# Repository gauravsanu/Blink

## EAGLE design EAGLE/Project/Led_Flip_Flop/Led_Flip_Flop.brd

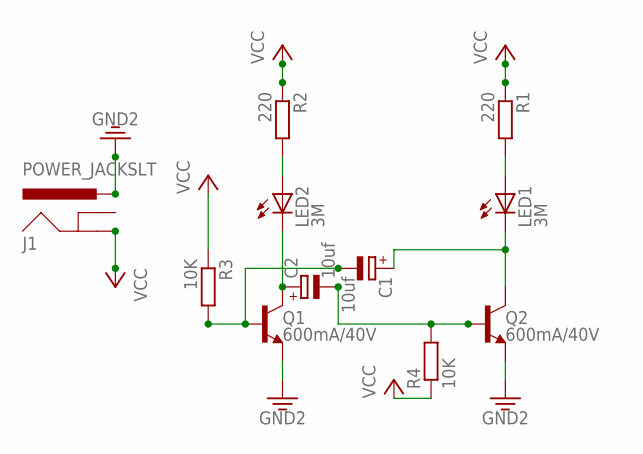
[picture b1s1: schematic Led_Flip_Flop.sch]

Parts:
C1, C2: 10uf; E1,8-4
J1: POWER_JACKSLT; POWER_JACK_SLOT
LED1, LED2: 3M; LED5MM
Q1, Q2: 600mA/40V; TO-92
R1, R2: 220; 0207/10
R3, R4: 10K; 0207/10

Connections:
3.3V: J1.PWR, Q1.3 (E), Q2.3 (E)
unnamed: LED2.A, R2.2
unnamed: LED1.A, R1.2
unnamed: C2.+, LED2.K (C), Q1.1 (C)
unnamed: C1.-, Q1.2 (B), R3.2
unnamed: C2.-, Q2.2 (B), R4.2
unnamed: C1.+, LED1.K (C), Q2.1 (C)
VCC: J1.GND@2 (GND), R1.1, R2.1, R3.1, R4.1

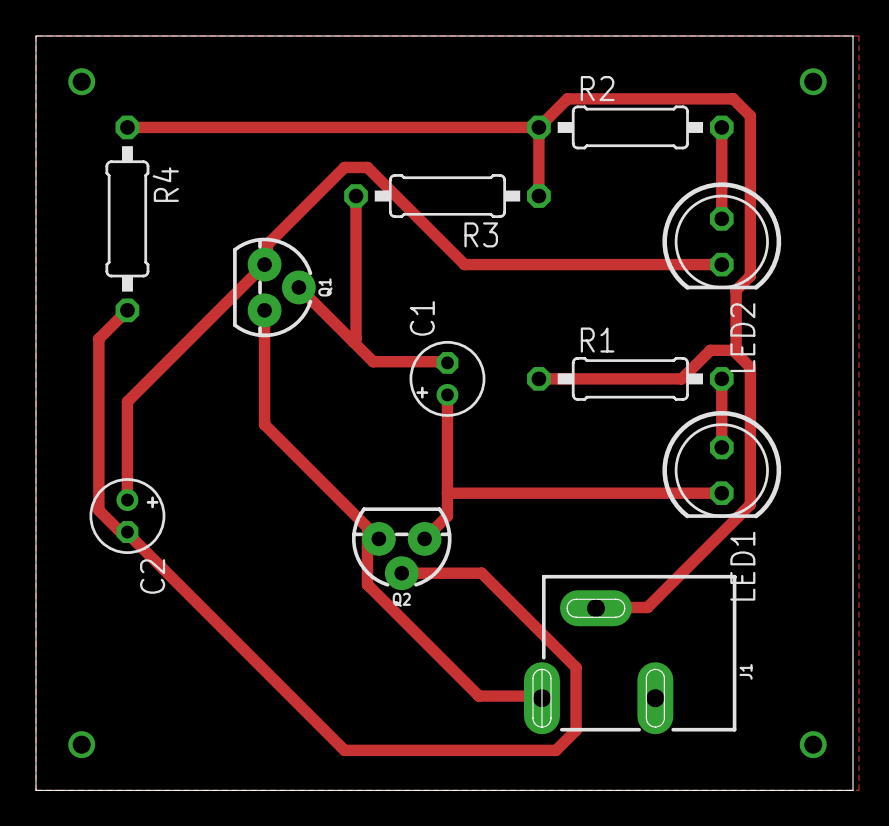
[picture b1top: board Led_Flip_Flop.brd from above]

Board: 2 copper layers, 45.4 x 41.9 mm, 11 parts (0 on the bottom side), 8 nets.

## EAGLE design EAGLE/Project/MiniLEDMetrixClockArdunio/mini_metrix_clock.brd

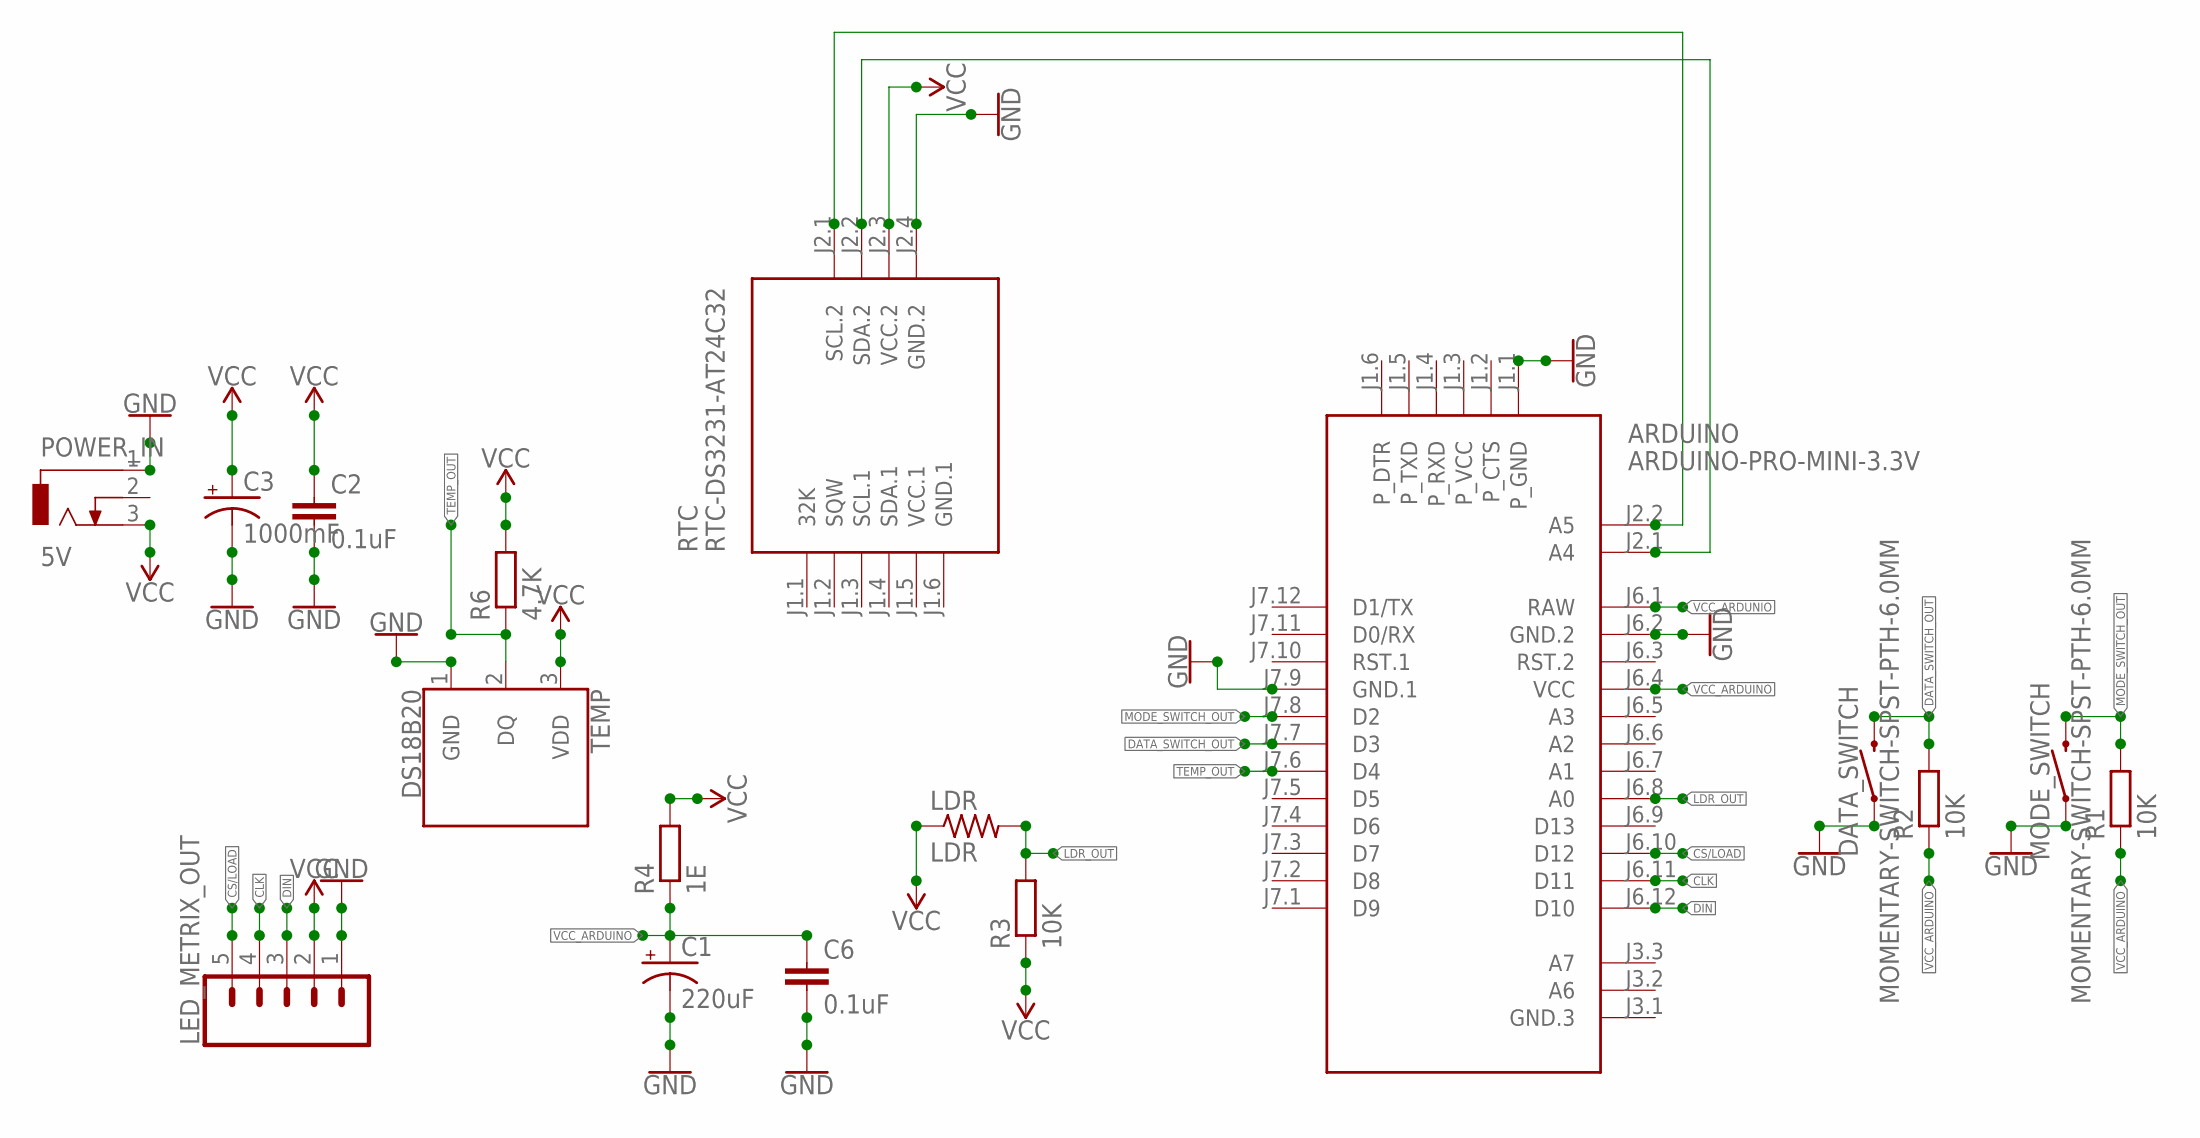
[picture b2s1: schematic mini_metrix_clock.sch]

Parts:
ARDUINO: ARDUINO-PRO-MINI-3.3V; ARDUINO-PRO-MINI
C1: 220uF; CPOL-RADIAL-2.5MM-6.5MM
C2, C6: 0.1uF; CAP-PTH-SMALL-KIT
C3: 1000mF; CPOL-RADIAL-5MM-10MM
DATA_SWITCH: MOMENTARY-SWITCH-SPST-PTH-6.0MM; TACTILE_SWITCH_PTH_6.0MM
LDR: LDR; 0204V
LED_METRIX_OUT: CONN_05PTH_LONGPADS; 1X05_LONGPADS
MODE_SWITCH: MOMENTARY-SWITCH-SPST-PTH-6.0MM; TACTILE_SWITCH_PTH_6.0MM
POWER_IN: 5V; DCJ0303
R1, R2, R3: 10K; 0207/7
R4: 1E; 0207/7
R6: 4.7K; 0207/7
RTC: RTC-DS3231-AT24C32
TEMP: DS18B20; TO-92-AMMO

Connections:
CLK: ARDUINO.J6.11 (D11), LED_METRIX_OUT.4
CS/LOAD: ARDUINO.J6.10 (D12), LED_METRIX_OUT.5
DATA_SWITCH_OUT: ARDUINO.J7.7 (D3), DATA_SWITCH.3 (2), R2.2
DIN: ARDUINO.J6.12 (D10), LED_METRIX_OUT.3
GND: ARDUINO.J1.1 (P_GND), ARDUINO.J6.2 (GND.2), ARDUINO.J7.9 (GND.1), C1.2 (-), C2.2, C3.-, C6.2, DATA_SWITCH.1, LED_METRIX_OUT.1, MODE_SWITCH.1, POWER_IN.1, RTC.J2.4 (GND.2), TEMP.1 (GND)
GND.1: RTC.J1.6 (GND.1)
LDR_OUT: ARDUINO.J6.8 (A0), LDR.2, R3.2
MODE_SWITCH_OUT: ARDUINO.J7.8 (D2), MODE_SWITCH.3 (2), R1.2
unnamed: ARDUINO.J2.1 (A4), RTC.J2.2 (SDA.2)
unnamed: ARDUINO.J2.2 (A5), RTC.J2.1 (SCL.2)
TEMP_OUT: ARDUINO.J7.6 (D4), R6.1, TEMP.2 (DQ)
VCC: C2.1, C3.+, LDR.1, LED_METRIX_OUT.2, POWER_IN.3, R3.1, R4.2, R6.2, RTC.J2.3 (VCC.2), TEMP.3 (VDD)
VCC.1: RTC.J1.5 (VCC.1)
VCC_ARDUINO: ARDUINO.J6.4 (VCC), C1.1 (+), C6.1, R1.1, R2.1, R4.1
VCC_ARDUNIO: ARDUINO.J6.1 (RAW)

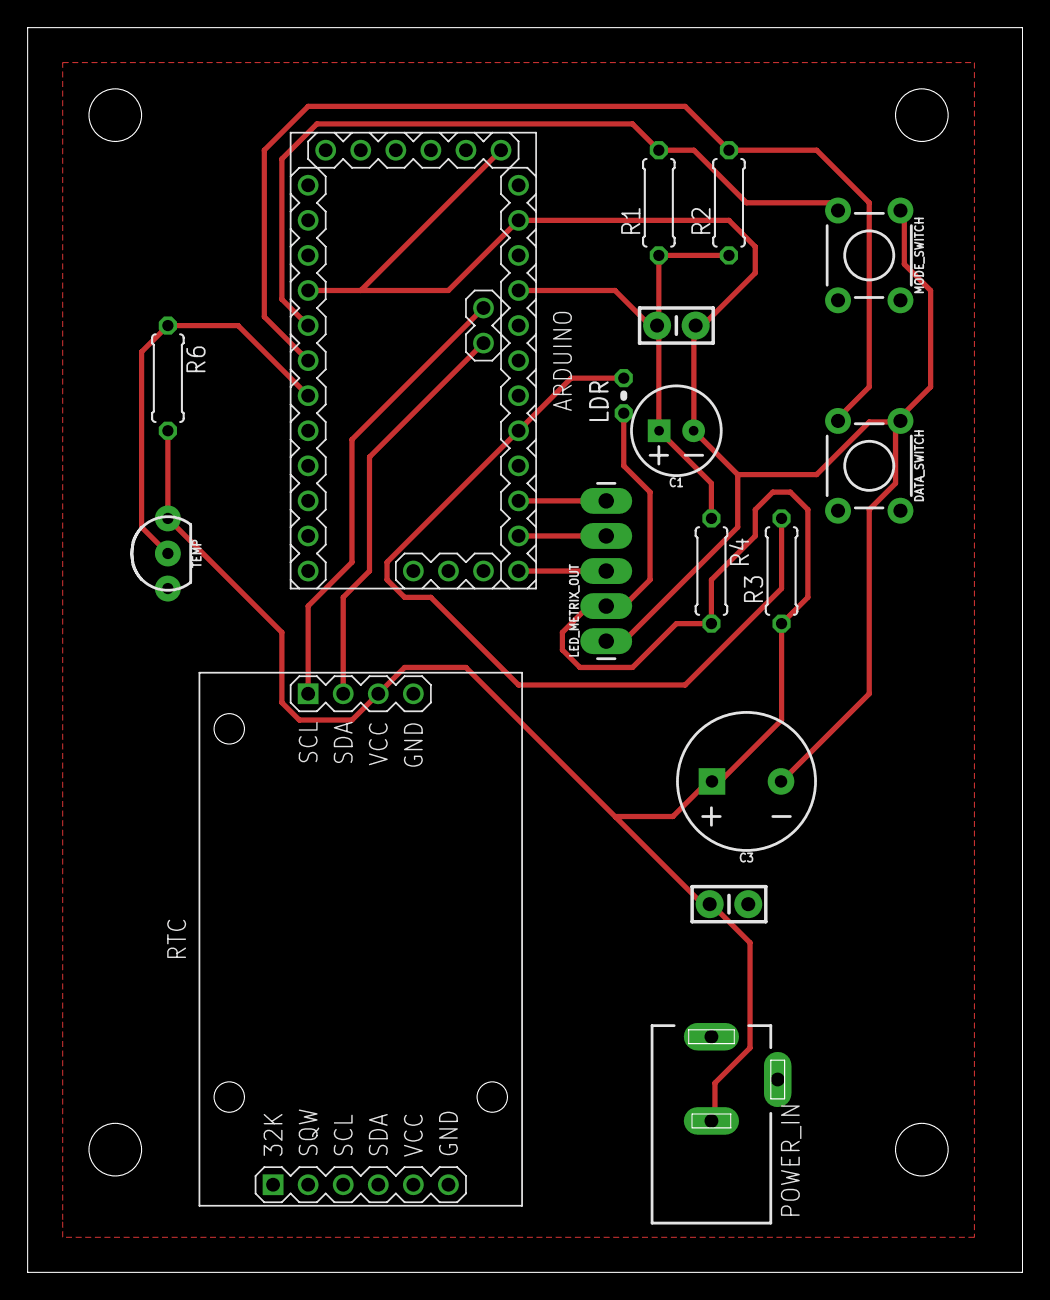
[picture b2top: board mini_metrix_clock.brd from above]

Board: 2 copper layers, 72.1 x 90.2 mm, 17 parts (0 on the bottom side), 12 nets.

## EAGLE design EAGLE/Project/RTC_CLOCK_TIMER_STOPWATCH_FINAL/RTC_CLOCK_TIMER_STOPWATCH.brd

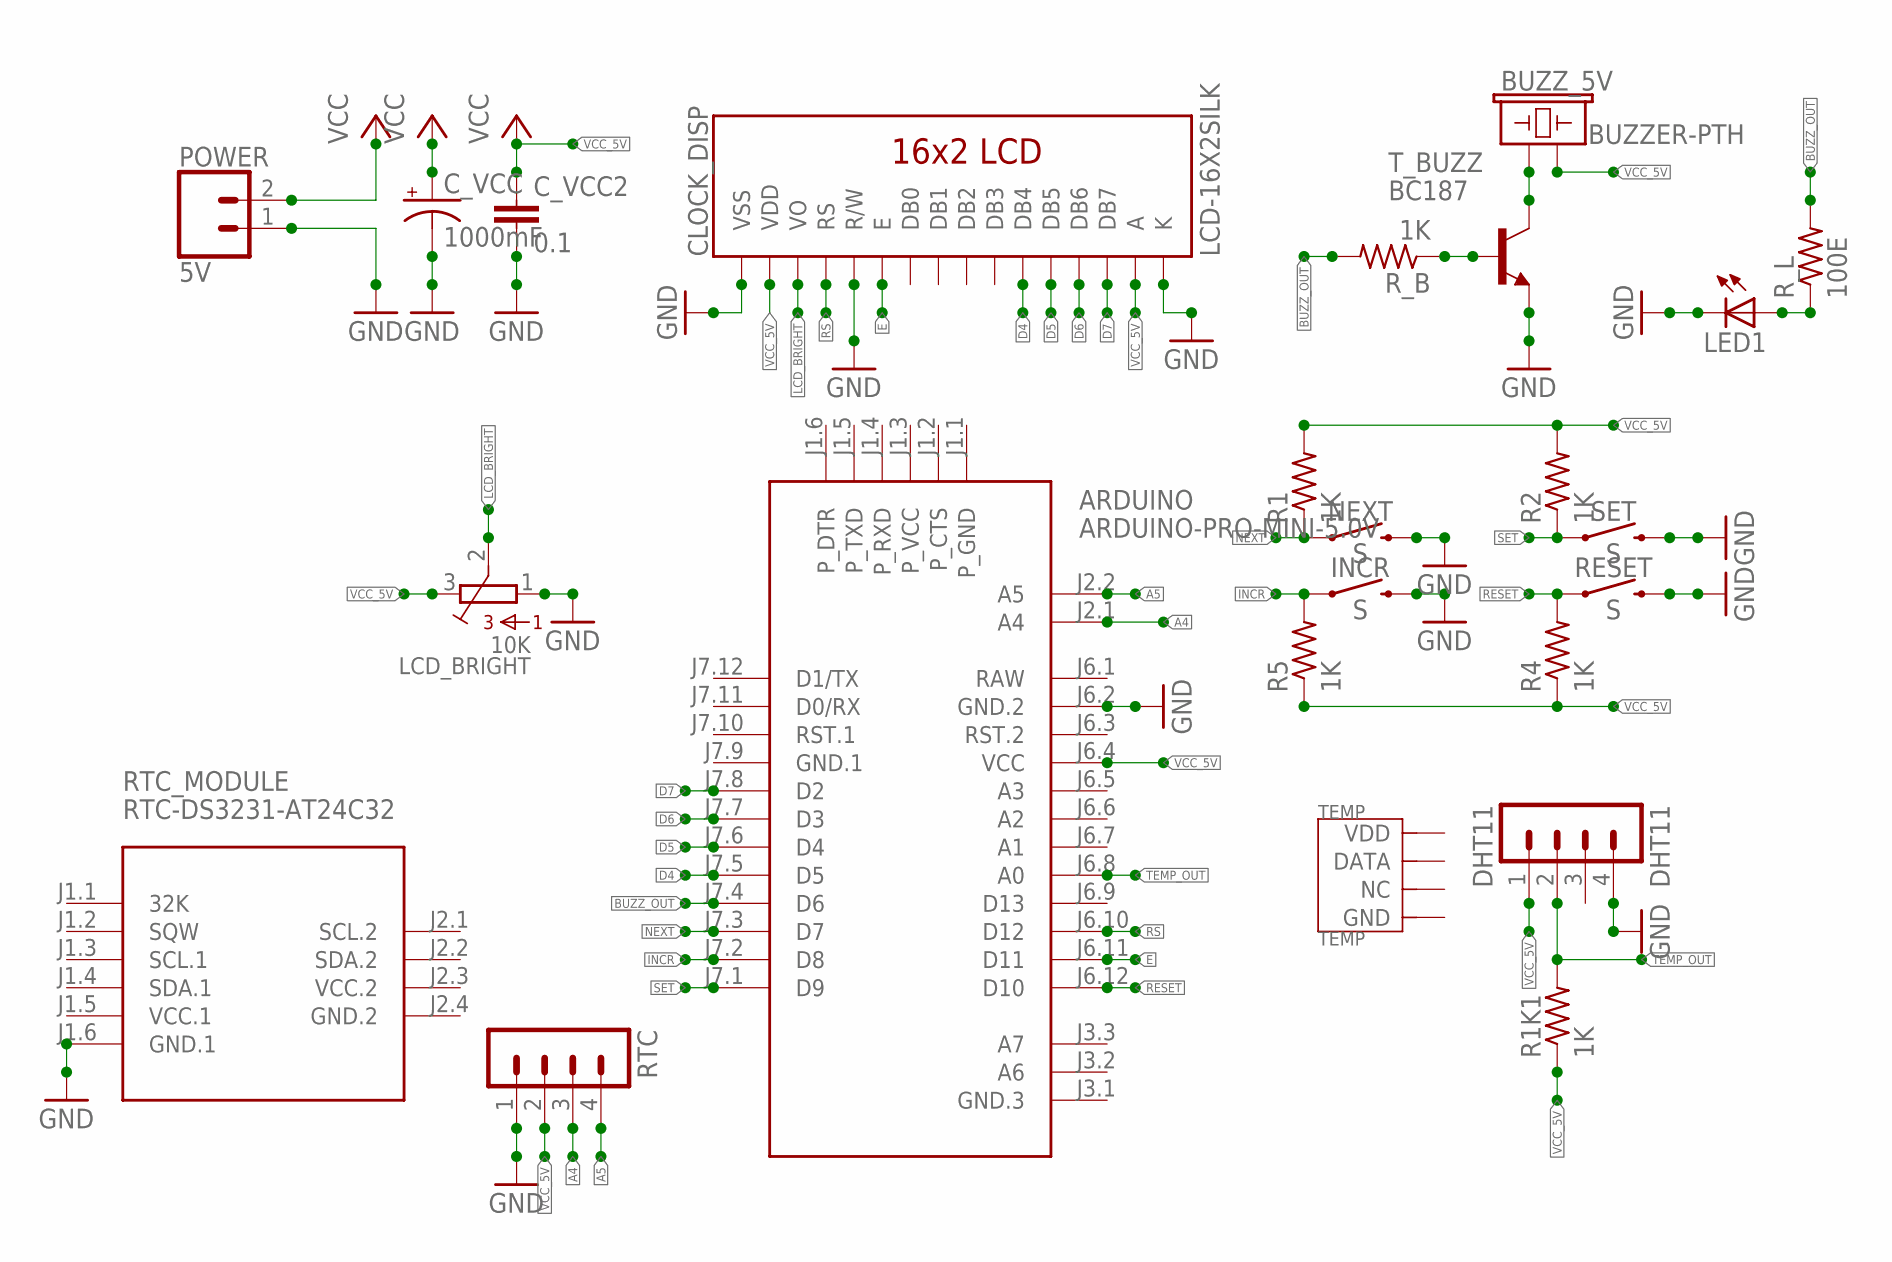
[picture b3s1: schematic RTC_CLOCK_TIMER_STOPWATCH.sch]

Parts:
ARDUINO: ARDUINO-PRO-MINI-5.0V; ARDUINO-PRO-MINI
BUZZ_5V: BUZZER-PTH; BUZZER-12MM
CLOCK_DISP: LCD-16X2SILK; LCD-16X2
C_VCC: 1000mF; CPOL-RADIAL-5MM-10MM
C_VCC2: 0.1; C050-024X044
DHT11: DHT11; MA04-1
INCR: S; TACTILE_SWITCH_PTH_6.0MM
LCD_BRIGHT: 10K; 3362P
LED1: LED5MM
NEXT: S; TACTILE_SWITCH_PTH_6.0MM
POWER: 5V; JST-2-PTH-KIT
R1, R1K1, R2, R4, R5: 1K; 0204/7
RESET: S; TACTILE_SWITCH_PTH_6.0MM
RTC: MA04-1
RTC_MODULE: RTC-DS3231-AT24C32
R_B: 1K; 0204/7
R_L: 100E; 0204/7
SET: S; TACTILE_SWITCH_PTH_6.0MM
TEMP: TEMP; SNR4-2.54-15.5X12.0X5.5MM
T_BUZZ: BC187; TO92-EBC-OVAL

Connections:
A4: ARDUINO.J2.1 (A4), RTC.3
A5: ARDUINO.J2.2 (A5), RTC.4
BUZZ_OUT: ARDUINO.J7.4 (D6), R_B.2, R_L.2
D4: ARDUINO.J7.5 (D5), CLOCK_DISP.11 (DB4)
D5: ARDUINO.J7.6 (D4), CLOCK_DISP.12 (DB5)
D6: ARDUINO.J7.7 (D3), CLOCK_DISP.13 (DB6)
D7: ARDUINO.J7.8 (D2), CLOCK_DISP.14 (DB7)
E: ARDUINO.J6.11 (D11), CLOCK_DISP.6 (E)
GND: ARDUINO.J6.2 (GND.2), CLOCK_DISP.1 (VSS), CLOCK_DISP.5 (R/W), CLOCK_DISP.16 (K), C_VCC.-, C_VCC2.2, DHT11.4, INCR.3 (2), LED1.K (C), NEXT.3 (2), POWER.1, RESET.3 (2), RTC.1, SET.3 (2), T_BUZZ.E
GND.1: ARDUINO.J7.9 (GND.1), RTC_MODULE.J1.6 (GND.1)
GND.2: RTC_MODULE.J2.4 (GND.2)
INCR: ARDUINO.J7.2 (D8), INCR.1, R5.2
LCD_BRIGHT: CLOCK_DISP.3 (VO), LCD_BRIGHT.2
unnamed: R_B.1, T_BUZZ.B
unnamed: BUZZ_5V.+ (1), T_BUZZ.C
unnamed: LED1.A, R_L.1
NEXT: ARDUINO.J7.3 (D7), NEXT.1, R1.1
RAW: ARDUINO.J6.1 (RAW)
RESET: ARDUINO.J6.12 (D10), R4.2, RESET.1
RS: ARDUINO.J6.10 (D12), CLOCK_DISP.4 (RS)
SET: ARDUINO.J7.1 (D9), R2.1, SET.1
TEMP_OUT: ARDUINO.J6.8 (A0), DHT11.2, R1K1.2
VCC: C_VCC.+, POWER.2
VCC.1: RTC_MODULE.J1.5 (VCC.1)
VCC.2: RTC_MODULE.J2.3 (VCC.2)
VCC_5V: ARDUINO.J6.4 (VCC), BUZZ_5V.- (2), CLOCK_DISP.2 (VDD), CLOCK_DISP.15 (A), C_VCC2.1, DHT11.1, LCD_BRIGHT.3, R1.2, R1K1.1, R2.2, R4.1, R5.1, RTC.2

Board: 2 copper layers, 24 parts (1 on the bottom side), 22 nets, no tracks yet.

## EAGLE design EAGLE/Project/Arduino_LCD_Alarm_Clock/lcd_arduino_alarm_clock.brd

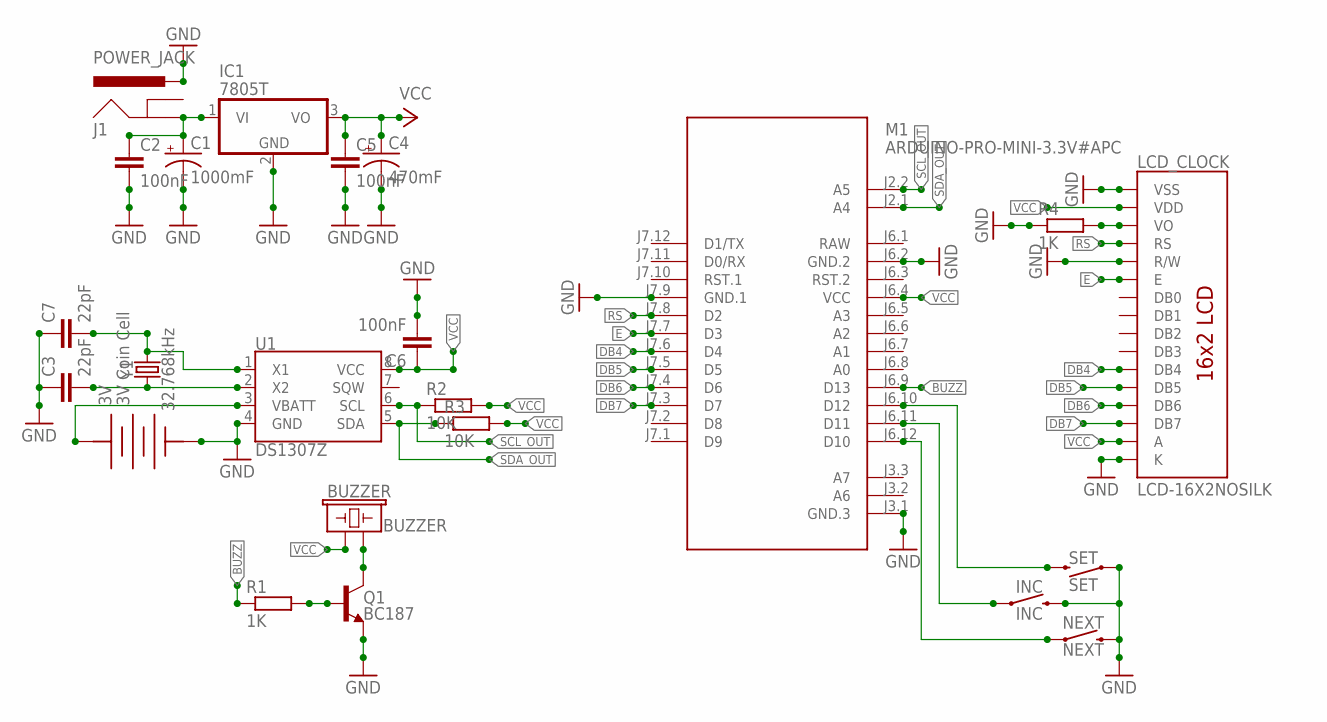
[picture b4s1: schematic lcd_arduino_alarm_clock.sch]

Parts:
3V: 3V Coin Cell; FKIT-LIR2450-H
BUZZER: BUZZER; BUZZER-12MM
C1: 1000mF; CPOL-RADIAL-5MM-10MM
C2, C5, C6: 100nF; 0603
C3, C7: 22pF; 0603
C4: 470mF; CPOL-RADIAL-5MM-10MM
IC1: 7805T; TO220H
INC: INC; TACTILE_SWITCH_PTH_6.0MM
J1: POWER_JACK; POWER_JACK_PTH
LCD_CLOCK: LCD-16X2NOSILK; LCD-16X2_NOSILK
M1: ARDUINO-PRO-MINI-3.3V#APC; ARDUINO-PRO-MINI#APC
NEXT: NEXT; TACTILE_SWITCH_PTH_6.0MM
Q1: BC187; TO-92
R1, R4: 1K; 0204/5
R2, R3: 10K; 0204/5
SET: SET; TACTILE_SWITCH_PTH_6.0MM
U1: DS1307Z; SO08-0.15
Y1: 32.768kHz; CRYSTAL-PTH-2X6-CYL

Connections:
BUZZ: M1.J6.9 (D13), R1.1
DB4: LCD_CLOCK.11 (DB4), M1.J7.6 (D4)
DB5: LCD_CLOCK.12 (DB5), M1.J7.5 (D5)
DB6: LCD_CLOCK.13 (DB6), M1.J7.4 (D6)
DB7: LCD_CLOCK.14 (DB7), M1.J7.3 (D7)
E: LCD_CLOCK.6 (E), M1.J7.7 (D3)
GND: 3V.NEG, C1.-, C2.2, C3.1, C4.-, C5.2, C6.2, C7.1, IC1.2 (GND), INC.3 (2), J1.PWR, LCD_CLOCK.1 (VSS), LCD_CLOCK.5 (R/W), LCD_CLOCK.16 (K), M1.J3.1 (GND.3), M1.J6.2 (GND.2), M1.J7.9 (GND.1), NEXT.3 (2), Q1.1 (E), R4.1, SET.1, U1.4 (GND)
unnamed: C1.+, C2.1, IC1.1 (VI), J1.GND
unnamed: LCD_CLOCK.3 (VO), R4.2
unnamed: C3.2, U1.2 (X2), Y1.1
unnamed: 3V.POS, U1.3 (VBATT)
unnamed: Q1.2 (B), R1.2
unnamed: M1.J6.10 (D12), SET.3 (2)
unnamed: INC.1, M1.J6.11 (D11)
unnamed: M1.J6.12 (D10), NEXT.1
unnamed: BUZZER.- (2), Q1.3 (C)
unnamed: C7.2, U1.1 (X1), Y1.2
RAW: M1.J6.1 (RAW)
RS: LCD_CLOCK.4 (RS), M1.J7.8 (D2)
SCL_OUT: M1.J2.2 (A5), R2.1, U1.6 (SCL)
SDA_OUT: M1.J2.1 (A4), R3.1, U1.5 (SDA)
VCC: BUZZER.+ (1), C4.+, C5.1, C6.1, IC1.3 (VO), LCD_CLOCK.2 (VDD), LCD_CLOCK.15 (A), M1.J6.4 (VCC), R2.2, R3.2, U1.8 (VCC)

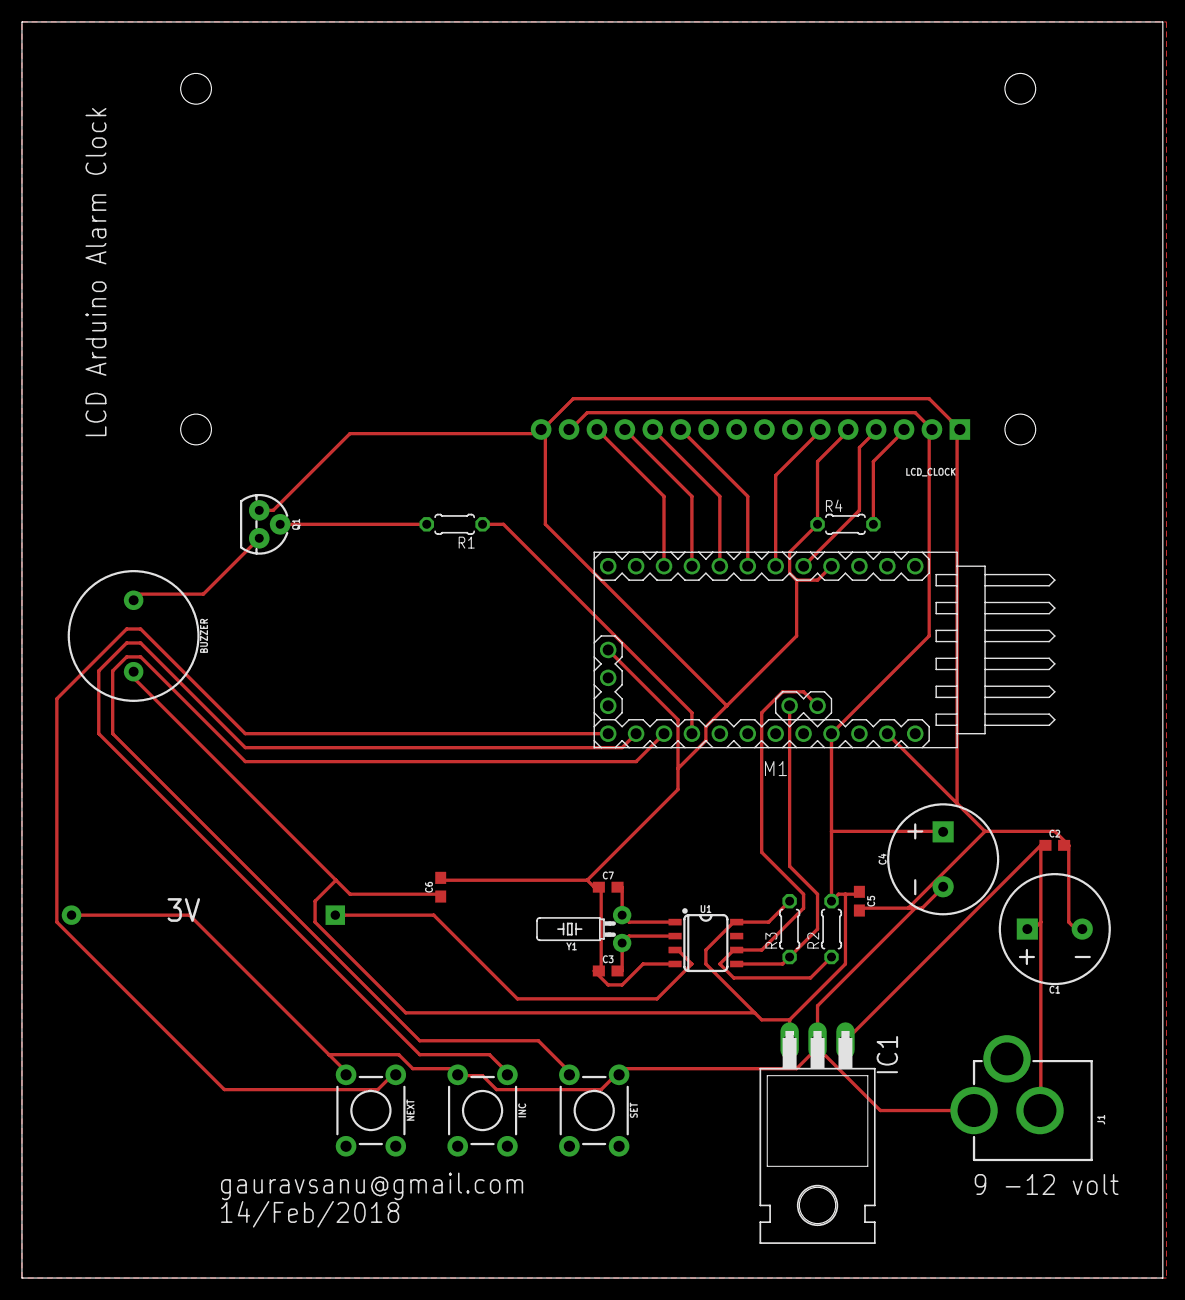
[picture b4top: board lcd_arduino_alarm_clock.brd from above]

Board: 2 copper layers, 103.8 x 114.3 mm, 23 parts (0 on the bottom side), 21 nets.

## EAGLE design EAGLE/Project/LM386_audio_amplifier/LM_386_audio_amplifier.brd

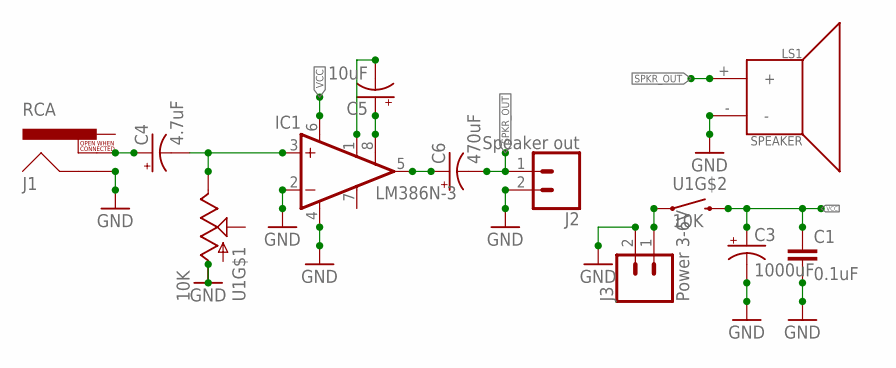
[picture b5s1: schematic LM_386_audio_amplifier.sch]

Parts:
C1: 0.1uF; 0603
C3: 1000uF; NIC_10X10.5_CAP
C4: 4.7uF; NIC_10X10.5_CAP
C5: 10uF; NIC_10X10.5_CAP
C6: 470uF; NIC_10X10.5_CAP
IC1: LM386N-3; DIL08
J1: RCA
J2: Speaker out; JST-2-PTH-NS
J3: Power 3-6V; JST-2-PTH-NS
LS1: SPEAKER; PCB_MOUNT_SPEAKER
U1: 10K; POT_PTH

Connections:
GND: C1.2, C3.-, IC1.2 (-IN), IC1.4 (GND), J1.SHELL, J2.2, J3.2, LS1.-, U1.E@1 (A)
unnamed: C4.-, IC1.3 (+IN), U1.E@2 (E)
unnamed: C4.+, J1.SWITCH
unnamed: C6.+, IC1.5 (OUT)
unnamed: C5.+, IC1.8 (GAIN)
unnamed: C5.-, IC1.1 (GAIN)
unnamed: J3.1, U1.S1 (1)
SPKR_OUT: C6.-, J2.1, LS1.+
VCC: C1.1, C3.+, IC1.6 (VS), U1.S2 (2)

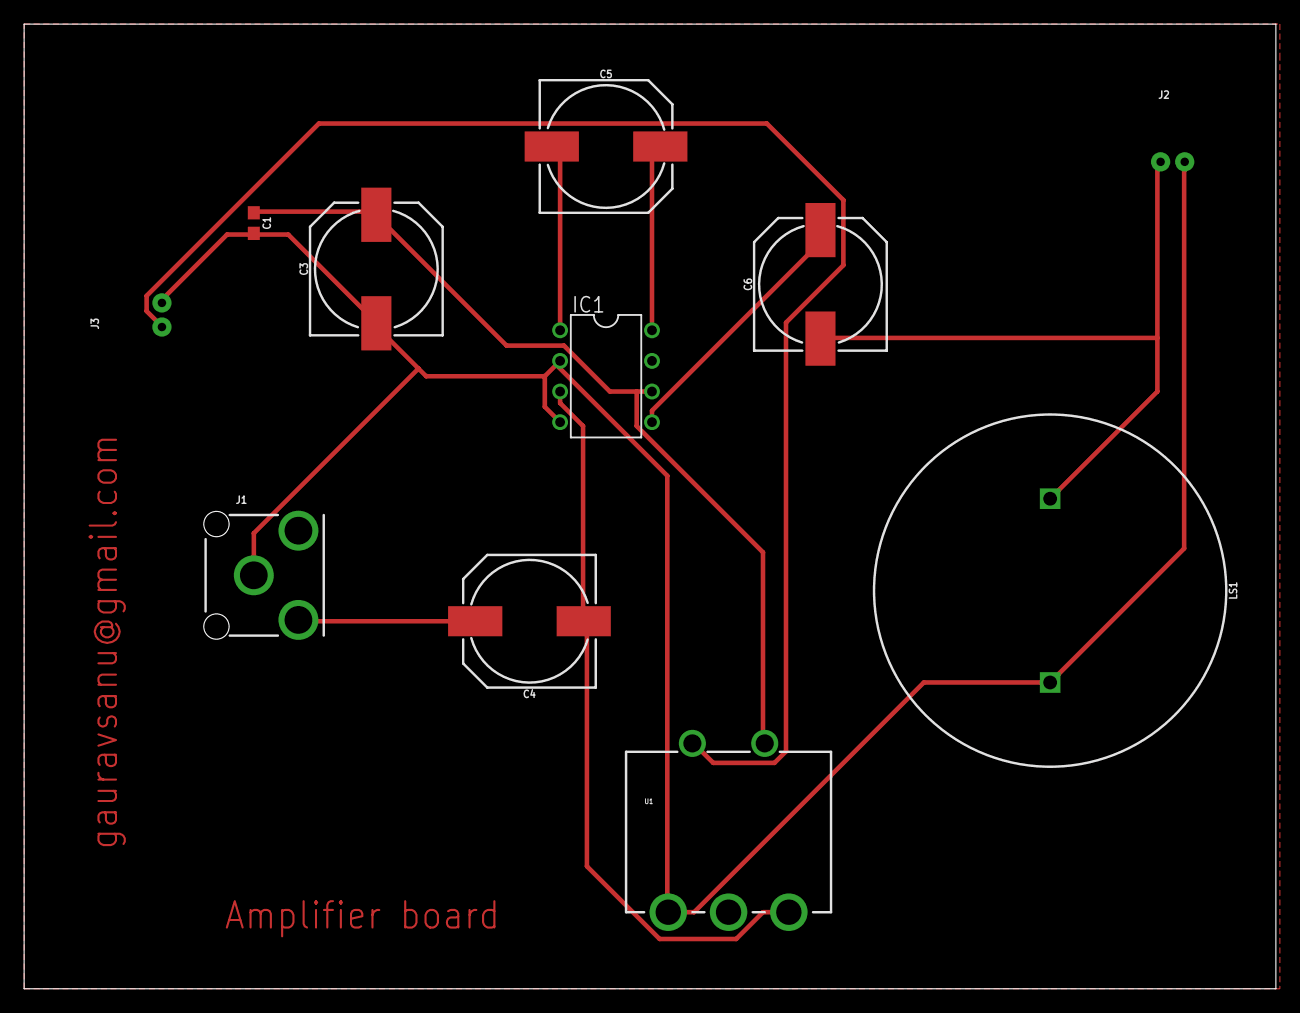
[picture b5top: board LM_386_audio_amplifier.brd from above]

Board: 2 copper layers, 103.8 x 80.0 mm, 11 parts (0 on the bottom side), 9 nets.

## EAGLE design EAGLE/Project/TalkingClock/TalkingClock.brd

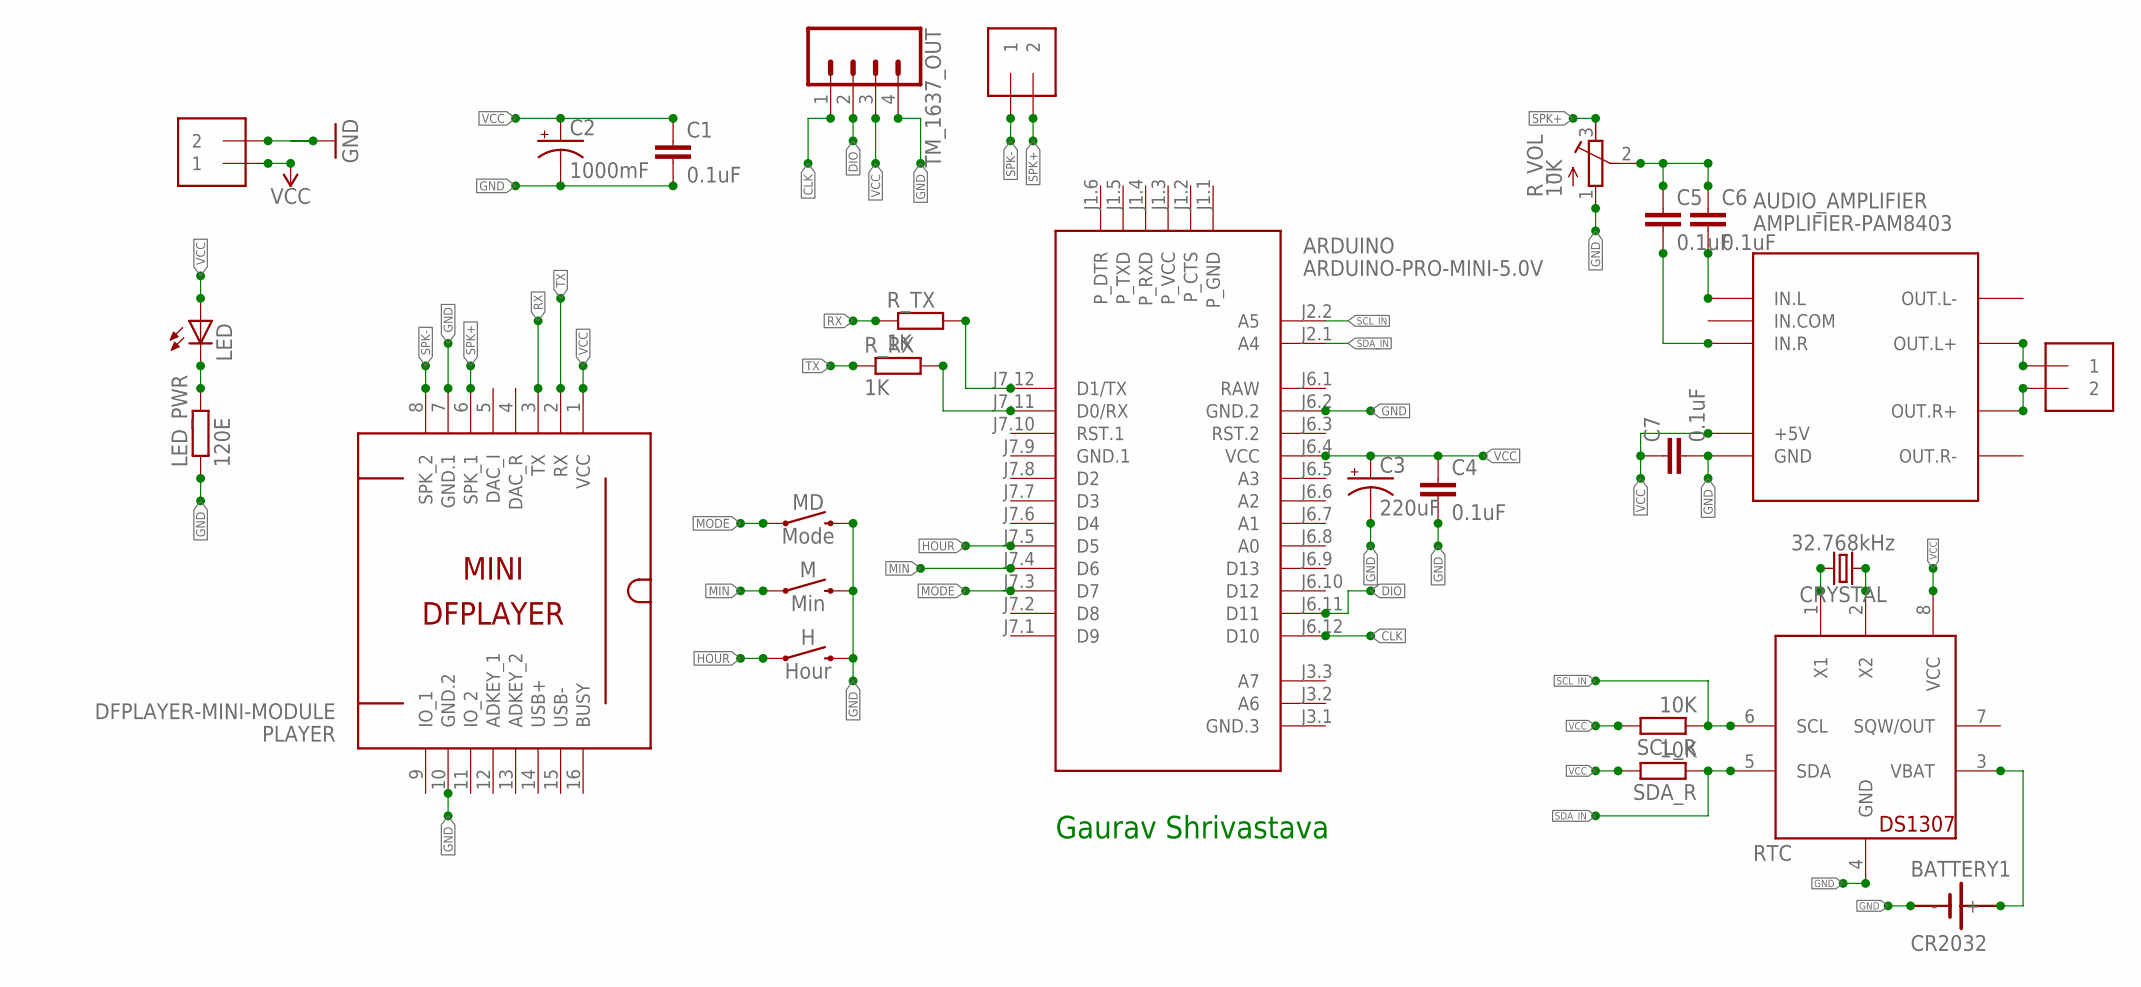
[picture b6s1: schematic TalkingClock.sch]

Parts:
ARDUINO: ARDUINO-PRO-MINI-5.0V; ARDUINO-PRO-MINI
AUDIO_AMPLIFIER: AMPLIFIER-PAM8403
BATTERY1: CR2032; SN2032
C1, C4, C5, C6, C7: 0.1uF; CAP-PTH-SMALL-KIT
C2: 1000mF; CPOL-RADIAL-5MM-10MM
C3: 220uF; CPOL-RADIAL-2.5MM-6.5MM
CRYSTAL: 32.768kHz; CRYSTAL-PTH-2X6-CYL
H: Hour; TACTILE_SWITCH_PTH_6.0MM
LED: LED5MM
LED_PWR: 120E; 0204/7
M: Min; TACTILE_SWITCH_PTH_6.0MM
MD: Mode; TACTILE_SWITCH_PTH_6.0MM
PLAYER: DFPLAYER-MINI-MODULE
POWER-5-V: SPEAKER; 1X2-3.5MM
PRE_SPK_OUT: SPEAKER; 1X2-3.5MM
RTC: DS1307; DIL08
R_RX: 1K; 0204/7
R_TX: 1K; 0204/7
R_VOL: 10K; RTRIM4G/J
SCL_R: 10K; 0204/7
SDA_R: 10K; 0204/7
SPEAKER: SPEAKER; 1X2-3.5MM
TM_1637_OUT: CONN_04; 1X04

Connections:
CLK: ARDUINO.J6.12 (D10), TM_1637_OUT.1
DIO: ARDUINO.J6.11 (D11), TM_1637_OUT.2
GND: ARDUINO.J6.2 (GND.2), AUDIO_AMPLIFIER.GND, BATTERY1.-, C1.2, C2.-, C3.2 (-), C4.2, C7.2, H.3 (2), LED_PWR.1, M.3 (2), MD.3 (2), PLAYER.7 (GND.1), PLAYER.10 (GND.2), POWER-5-V.2, RTC.4 (GND), R_VOL.1 (A), TM_1637_OUT.4
GND.1: ARDUINO.J7.9 (GND.1)
HOUR: ARDUINO.J7.5 (D5), H.1
MIN: ARDUINO.J7.4 (D6), M.1
MODE: ARDUINO.J7.3 (D7), MD.1
unnamed: ARDUINO.J7.12 (D1/TX), R_TX.2
unnamed: ARDUINO.J7.11 (D0/RX), R_RX.2
unnamed: LED.K (C), LED_PWR.2
unnamed: CRYSTAL.2, RTC.1 (X1)
unnamed: CRYSTAL.1, RTC.2 (X2)
unnamed: AUDIO_AMPLIFIER.IN.L, C6.2
unnamed: AUDIO_AMPLIFIER.IN.R, C5.2
unnamed: AUDIO_AMPLIFIER.OUT.L+, SPEAKER.1
unnamed: AUDIO_AMPLIFIER.OUT.R+, SPEAKER.2
unnamed: BATTERY1.+, RTC.3 (VBAT)
RAW: ARDUINO.J6.1 (RAW)
RX: PLAYER.3 (TX), R_TX.1
SCL_IN: ARDUINO.J2.2 (A5), RTC.6 (SCL), SCL_R.1
SDA_IN: ARDUINO.J2.1 (A4), RTC.5 (SDA), SDA_R.1
SPK+: C5.1, C6.1, PLAYER.6 (SPK_1), PRE_SPK_OUT.2, R_VOL.2 (S), R_VOL.3 (E)
SPK-: PLAYER.8 (SPK_2), PRE_SPK_OUT.1
TX: PLAYER.2 (RX), R_RX.1
VCC: ARDUINO.J6.4 (VCC), AUDIO_AMPLIFIER.+5V, C1.1, C2.+, C3.1 (+), C4.1, C7.1, LED.A, PLAYER.1 (VCC), POWER-5-V.1, RTC.8 (VCC), SCL_R.2, SDA_R.2, TM_1637_OUT.3

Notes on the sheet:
Gaurav Shrivastava

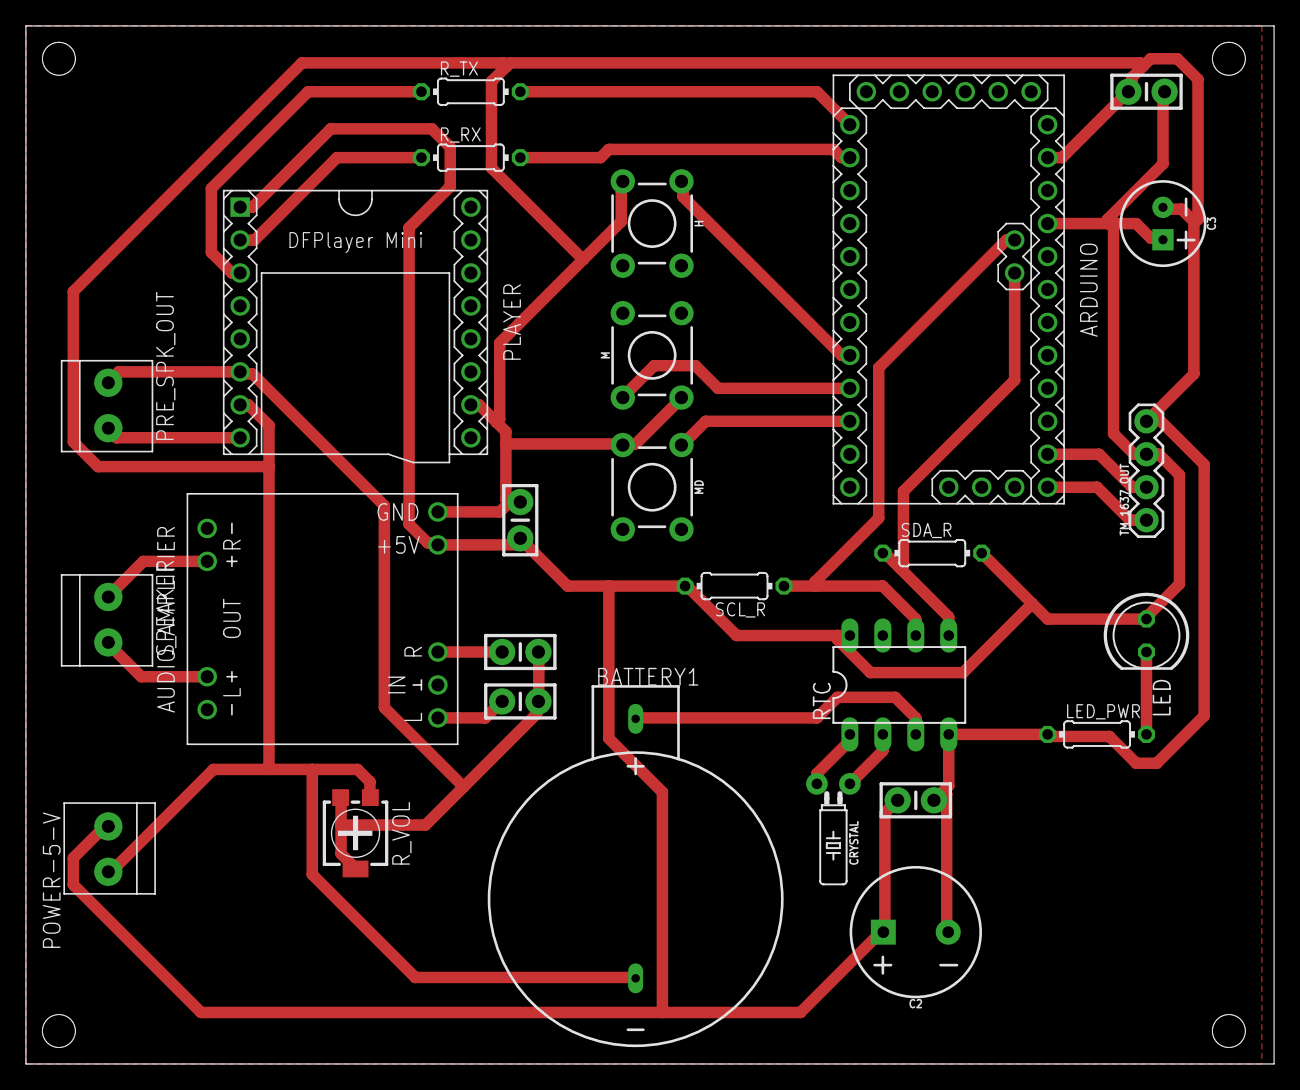
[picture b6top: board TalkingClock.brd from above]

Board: 2 copper layers, 96.2 x 80.0 mm, 27 parts (0 on the bottom side), 23 nets.

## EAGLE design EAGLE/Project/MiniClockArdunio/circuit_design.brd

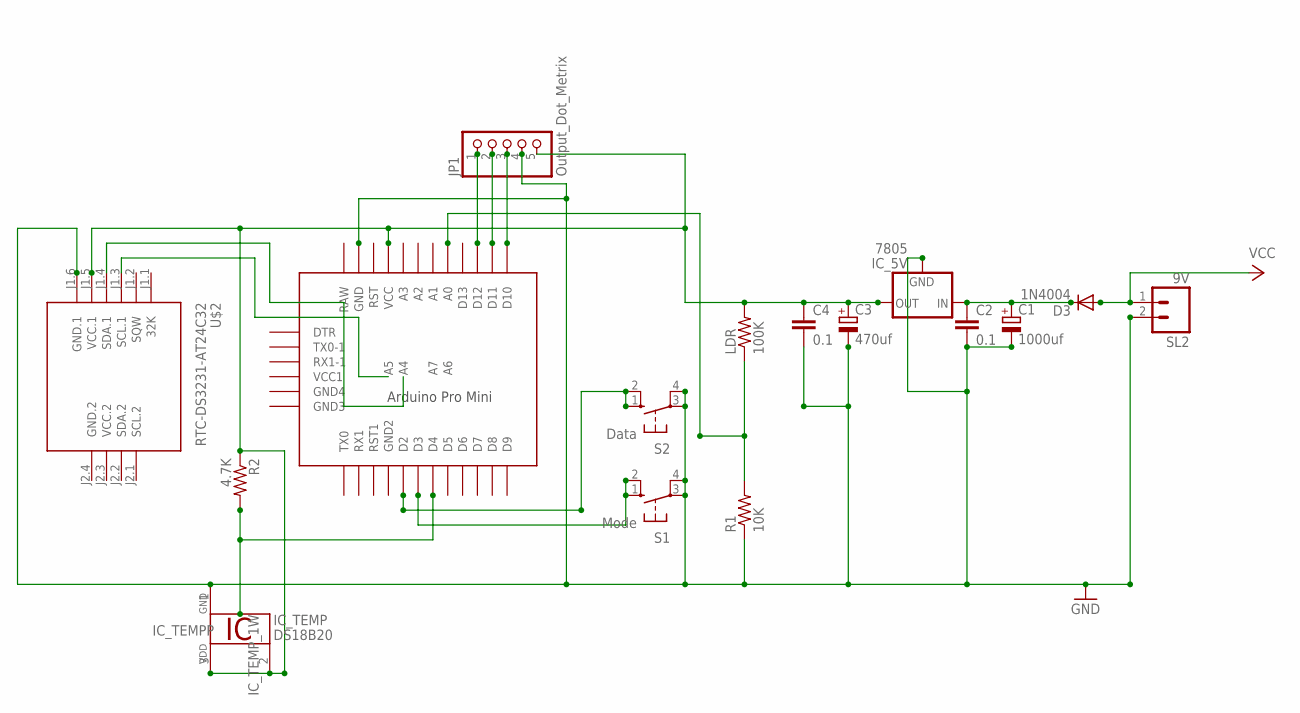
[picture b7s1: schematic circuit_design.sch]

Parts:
C1: 1000uf; E2,5-6E
C2, C4: 0.1; C025-024X044
C3: 470uf; E2,5-6E
D3: 1N4004; DO41-10
IC_5V: 7805; 78XXS
IC_TEMP: DS18B20; TO92-
JP1: Output_Dot_Metrix; 1X05
LDR: 100K; V526-0
R1: 10K; 0309/12
R2: 4.7K; 0309/12
S1: Mode; B3F-10XX
S2: Data; B3F-10XX
SL2: 9V; 02P
U$1: PRO-MINI-2
U$2: RTC-DS3231-AT24C32

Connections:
GND: C1.-, C2.2, C3.-, C4.2, IC_5V.GND, IC_TEMP.1 (GND), JP1.4, R1.1, S1.3, S1.4 (P1), S2.3, S2.4 (P1), SL2.2, U$1.GND, U$2.J1.6 (GND.1)
GND.2: U$2.J2.4 (GND.2)
unnamed: C1.+, C2.1, D3.C, IC_5V.IN
unnamed: C3.+, C4.1, IC_5V.OUT, IC_TEMP.2 (1W), IC_TEMP.3 (VDD), JP1.5, LDR.2, R2.1, U$1.VCC, U$2.J1.5 (VCC.1)
unnamed: S2.1 (S), S2.2 (S1), U$1.D2
unnamed: LDR.1, R1.2, U$1.A0
unnamed: S1.1 (S), S1.2 (S1), U$1.D3
unnamed: R2.2, U$1.D4
unnamed: JP1.1, U$1.D12
unnamed: JP1.2, U$1.D11
unnamed: JP1.3, U$1.D10
VCC: D3.A, SL2.1
VCC.2: U$2.J2.3 (VCC.2)

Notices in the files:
parts and their libraries:
SparkFun-Retired: Licensing: Creative Commons ShareAlike 4.0 International - https://creativecommons.org/licenses/by-sa/4.0
diy-modules: Released under the Creative Commons Attribution 4.0 International License: http://creativecommons.org/licenses/by/4.0
